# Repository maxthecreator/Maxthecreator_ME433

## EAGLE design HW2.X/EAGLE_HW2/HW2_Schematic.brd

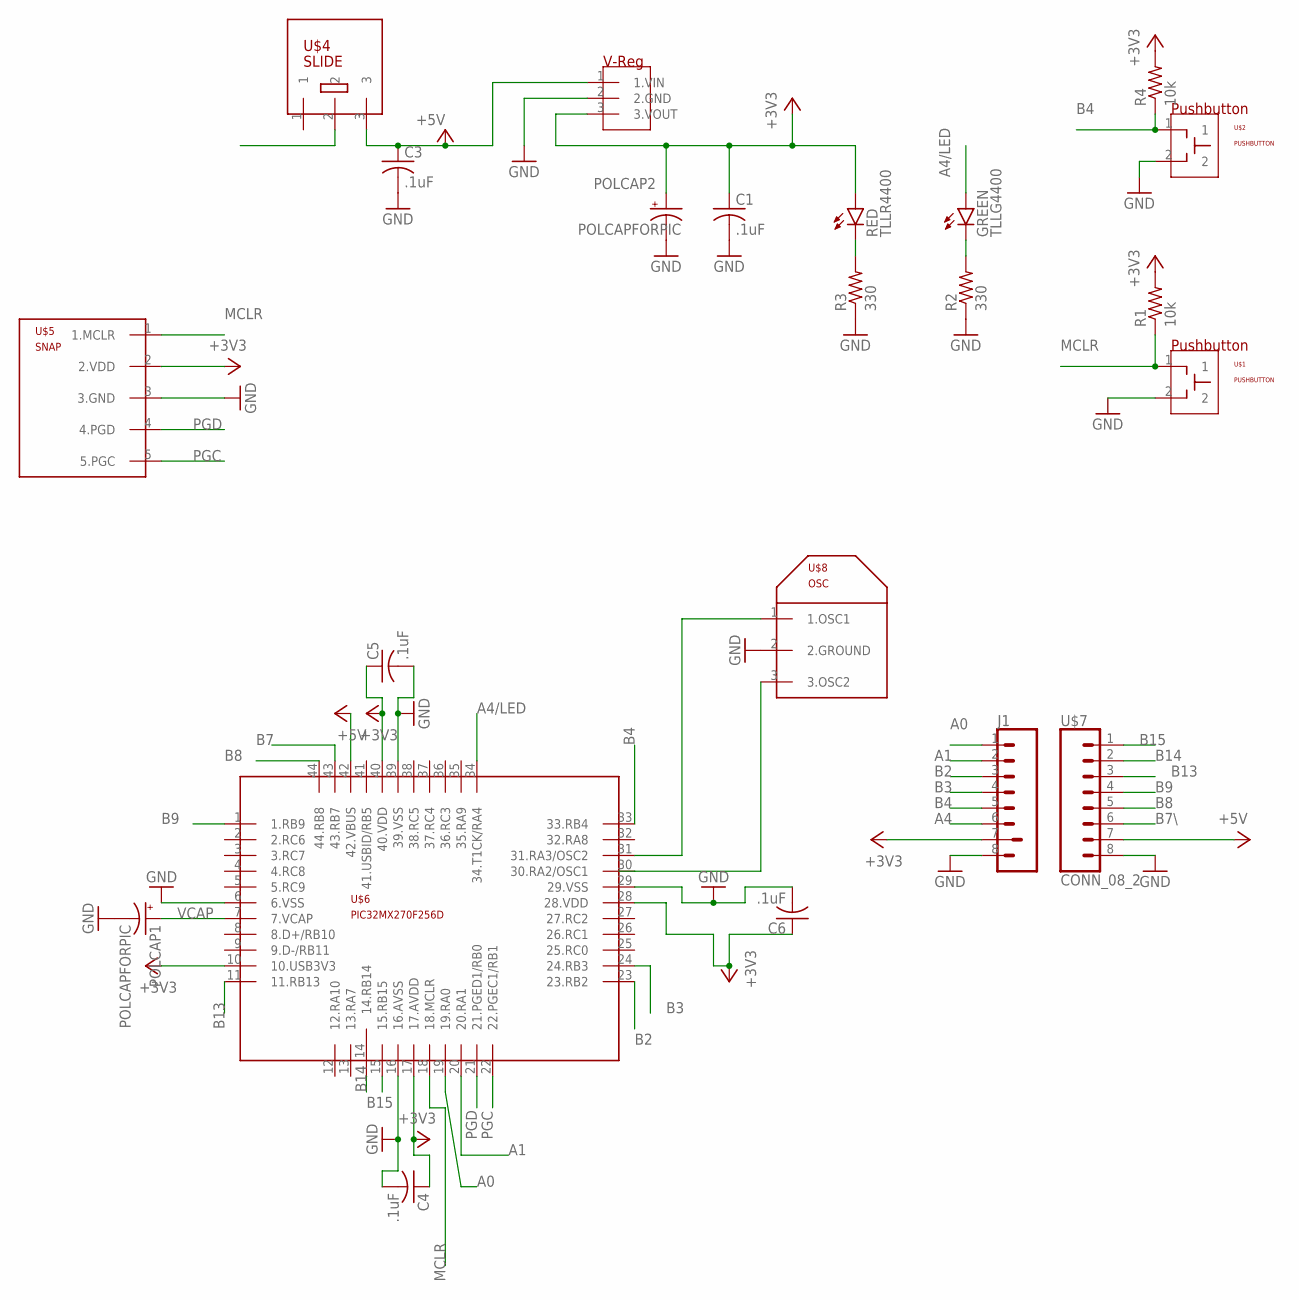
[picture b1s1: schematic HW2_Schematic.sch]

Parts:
C1, C3: .1uF; C025-030X050
C4, C5, C6: .1uF; C025-024X044
GREEN: TLLG4400; LED3MM
J1: CONN_08; CONN08
POLCAP1, POLCAP2: POLCAPFORPIC; POLARIZEDCAPFORPIC
R1, R4: 10k; 0207/10
R2, R3: 330; 0207/10
RED: TLLR4400; LED3MM
U$1, U$2: PUSHBUTTON
U$3: VOTAGEREG; V-REG
U$4: SLIDE
U$5: SNAP
U$6: PIC32MX270F256D; PIC_44-PIN
U$7: CONN_08_2; CONN08
U$8: OSC

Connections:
+3V3: C1.1, C4.1, C5.1, C6.1, J1.7 (7.3V3), POLCAP2.1 (+), R1.2, R4.2, RED.A, U$3.3 (3.VOUT), U$5.2 (2.VDD), U$6.10 (10.USB3V3), U$6.17 (17.AVDD), U$6.28 (28.VDD), U$6.40 (40.VDD)
+5V: C3.1, U$3.1 (1.VIN), U$4.3, U$6.42 (42.VBUS), U$7.7 (7.5V)
A0: J1.1 (1.A0), U$6.19 (19.RA0)
A1: J1.2 (2.A1), U$6.20 (20.RA1)
A4: J1.6 (6.A4)
A4/LED: GREEN.A, U$6.34 (34.T1CK/RA4)
B2: J1.3 (3.B2), U$6.23 (23.RB2)
B3: J1.4 (4.B3), U$6.24 (24.RB3)
B4: J1.5 (5.B4), R4.1, U$2.1, U$6.33 (33.RB4)
B7: U$6.43 (43.RB7)
B7\: U$7.6 (6.B7)
B8: U$6.44 (44.RB8), U$7.5 (5.B8)
B9: U$6.1 (1.RB9), U$7.4 (4.B9)
B13: U$6.11 (11.RB13), U$7.3 (3.B13)
B14: U$6.14 (14.RB14), U$7.2 (2.B14)
B15: U$6.15 (15.RB15), U$7.1 (1.B15)
GND: C1.2, C3.2, C4.2, C5.2, C6.2, J1.8 (8.GND), POLCAP1.2 (-), POLCAP2.2 (-), R2.1, R3.1, U$1.2, U$2.2, U$3.2 (2.GND), U$5.3 (3.GND), U$6.6 (6.VSS), U$6.16 (16.AVSS), U$6.29 (29.VSS), U$6.39 (39.VSS), U$7.8 (8.GND), U$8.2 (2.GROUND)
MCLR: R1.1, U$1.1, U$5.1 (1.MCLR), U$6.18 (18.MCLR)
unnamed: GREEN.K (C), R2.2
unnamed: R3.2, RED.K (C)
unnamed: U$6.30 (30.RA2/OSC1), U$8.3 (3.OSC2)
unnamed: U$6.31 (31.RA3/OSC2), U$8.1 (1.OSC1)
PGC: U$5.5 (5.PGC), U$6.22 (22.PGEC1/RB1)
PGD: U$5.4 (4.PGD), U$6.21 (21.PGED1/RB0)
VCAP: POLCAP1.1 (+), U$6.7 (7.VCAP)

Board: 2 copper layers, 22 parts (0 on the bottom side), 22 nets, no tracks yet.

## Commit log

2019-04-03 Getting Started (1)
2019-04-03 Opened main.c
    opened and deleted all contents
2019-04-03 first attempt
2019-04-04 Setting Pragma values
2019-04-04 Set lat, tris
2019-04-04 First draft finished
2019-04-04 Final changes 4/3
2019-04-11 HW1 Screenshots
2019-04-11 HW2 UPLOAD
2019-04-15 hw4 update
2019-04-15 updated set_voltage
2019-04-15 trying to figure out set_voltage
    using t1 and t2 for the first and second bytes for the transfer
2019-04-15 another try
2019-04-15 finished hw1
2019-04-16 Finished first draft of spi
2019-04-16 Got the outputs working. no sine or triangle wave yet
2019-04-18 Added waves to hw4
2019-04-18 trying to debug
2019-04-18 cant figure it outtt
2019-04-18 fixed spi!
2019-04-18 started hw5
2019-04-21 getting strange errors when compiling
2019-04-21 try again
2019-04-21 third
2019-04-21 turned the light on, cant do getExpander()
2019-04-21 started 6
2019-04-21 works in reverse
2019-04-21 finished 5
2019-04-23 finished 6
2019-04-24 hw7 start
2019-04-25 reading registers
2019-04-25 one more
2019-04-25 added lcd
2019-04-25 tried ili2
2019-04-26 add bar
2019-04-26 got the bars to work!
2019-04-26 adjusting bar locations
2019-04-26 done
2019-04-29 started 8
2019-04-29 part 1 done
2019-04-29 try try again!
2019-05-01 first shot
2019-05-01 got pix
2019-05-02 done?
2019-05-06 finished touchscreen
2019-05-07 finished 8
2019-05-07 hw10 started
2019-05-07 hw10
2019-05-10 hw10 continued
2019-05-10 lost it?
2019-05-10 done with 10!
2019-05-10 yaas
2019-05-10 attempting to get 11 set up
2019-05-11 can't fix 11
2019-05-13 hw11
2019-05-13 hw12
2019-05-13 hw12 done
2019-05-13 no change
2019-05-21 hw13
2019-05-21 plot added
2019-05-21 added design
2019-05-29 15 started
2019-05-29 continuing 15
2019-05-30 worked on interrupt
2019-06-04 hw15 working but math is weird
2019-06-05 hw15 complete
2019-06-10 techcup
2019-06-12 tech cup!
2019-06-12 added pictures and DXF
